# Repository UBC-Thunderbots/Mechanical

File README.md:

# Mechanical
Our mechanical CAD repository. To get started, please see follow the guide below:

## Setting Up with GitHub Desktop:
*Using GitHub Desktop is the simplest method. You're welcome to try other options

1. Download [GitHub Desktop](https://desktop.github.com/)
2. Create an account or login.
3. Go to the [Thunderbot's mechanical repository](https://github.com/UBC-Thunderbots/Mechanical) on GitHub.
4. Click on the green ```<> Code``` button and click: ```Open with GitHub Desktop```
5. Click Choose... and navigate to a local directory where you want to clone the repository. *Note that this location will be where a local copy of the entire CAD file will be stored.
6. Click Clone.
7. Ask to be added as a collaborator to the repository.

By now, you should have a local copy of the entire mechanical CAD folder.

## Workflow: Updating your local folder:

Before you make any changes to the mechanical assembly, it is important that you update your local CAD folder with any changes that may have been made by someone else so you are working with the most up-to-date mechanical assembly.

1. **On GitHub Desktop** click ```fetch```. This will _fetch_ any changes that have been made to the remote repository to you computer, without actually updating your local folder yet.

After fetching, you should be notified whether there are any merge conflicts. In other words, whether there have been any changes made to files that you have also modified on your local folder.

If there is a merge conflict:
1. Give-up. :(

If there is no merge conflict:
1. Click on ```Pull Origin``` and your local folder should automatically be updated to reflect any changes on the remote repository.

## Workflow: Updating your changes to the remote repository:

If you have any new changes, they should show up in your **GitHub Desktop** application under "Changed Files" - otherwise, you did something wrong.
1. Start off with ```committing to main```. Name the change you made under Summary _(e.g. New Dribbler Design)_.
2. After it commits successfully, the button at the top should read ```Push Origin```
3. Click on it. Do make sure that **nobody else is/was working on the same file you did - communicate this clearly before moving forward.**

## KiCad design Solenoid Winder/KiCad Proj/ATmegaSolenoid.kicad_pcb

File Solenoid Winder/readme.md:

# Solenoid Winding Machine - Standard Operating Procedure (SOP)
*Last revised: 7th June 2026 by Thomas Frew*

## Overview
*(Refer to CAD overviews of the winder and director assemblies)*

## Winding Instructions

### Wiring and Setup
Ensure the breadboard, solenoid winder motors, and Arduino Uno are wired as shown in the reference diagrams.
- Make all I/O connections shown in the table below. 
- Regarding the breadboard, buttons are LEFT, RIGHT, ENTER, BACK, from left to right.
- The motor controller board with the larger heatsink must be connected to the chuck motor*.

*Stepper motor connected to chuck: pins 1&3 are coil A and 4&6 are coil B. Stepper motor for lead screw: pins 1&4 are coil A and 3&6 are coil B.

### I/O Connections Table

| Input | Arduino Connection |
| :--- | :--- |
| Left_button | Digital Pin 0 |
| Right_button | Digital Pin 2 |
| Back_button | Digital Pin 3 |
| Enter_button | Digital Pin 4 |
| Lead_STEP | Digital Pin 5 |
| Lead_DIR | Digital Pin 6 |
| Chuck_STEP | Digital Pin 7 |
| Chuck_DIR | Digital Pin 8 |
| Lead_MS1 | Digital Pin 9 |
| Lead_MS2 | Digital Pin 10 |
| Lead_MS3 | Digital Pin 11 |
| +ve breadboard rail | +5V |
| -ve breadboard rail | GND |

### Step-by-Step Operation

1. Go to [https://github.com/Thoamy/SolenoidWinder](https://github.com/Thoamy/SolenoidWinder) and download `SolenoidWindingMachine_V1.ino`.
2. You will need the Arduino IDE to load the project onto your Arduino.
3. Ensure you have the correctly sized Chuck Adapter and Tailstock Adapter to match your Solenoid Housing.
4. Insert the Chuck Adapter and Tailstock Adapter into the Solenoid Housing (Chuck Adapter on the side with the coil escape hole), then install the assembly into the chuck/tailstock.
5. **Note on 3D Printing:** If you need to 3D print new adapters, ensure the Chuck adapter is printed oriented in a horizontal position (the position used) for torque transfer, and the Tailstock Adapter is printed in the vertical position for axial load bearing.
6. Load your roll of copper onto the Spool Holder subassembly. Use two nuts to hold the roll on, but do not tension the roll.
7. If necessary, loosen the captive nut on the Director Assembly and adjust the Director to be as close to the solenoid as possible, ensuring that the solenoid will never collide with the Director Assembly during rotation.
8. Feed the copper through the Director large hole, through 2-3 layers of foam, then through the Director small hole.
9. Use pliers to feed the copper through the escape hole of the Solenoid Housing.
10. Plug the Arduino USB into your computer (load the program if not done), and plug the 12V wall adapter barrel jack into the barrel jack adapter (plugged into the breadboard).
    - **⚠️ WARNING: DO NOT MIX +5V AND +12V OR YOU WILL FRY YOUR ARDUINO.**
11. During winding, make sure the first layer is super tight (slide the coils down with your hands if needed) so that the subsequent layers stack nicely on top.

## Controls
- **Left:** Moves left while rotating chuck.
- **Right:** Moves right while rotating chuck.
- **Enter + Right/Left (Hold):** Disengages the chuck and moves left/right.
- *Note:* If you need to unwind (or manually spin the motor for any reason), **turn off power and then unplug the motor first**.

## Troubleshooting
- **The motor is going the wrong way:** Swap a set of A/B lines on the breadboard (either 1 or 2, not both).
- **The chuck is jerking in different directions:** One of the coil lines has likely become unplugged from the breadboard.
- **The copper crossed over itself:** Turn off power, unplug the motor, unwind, plug back in, and try again.

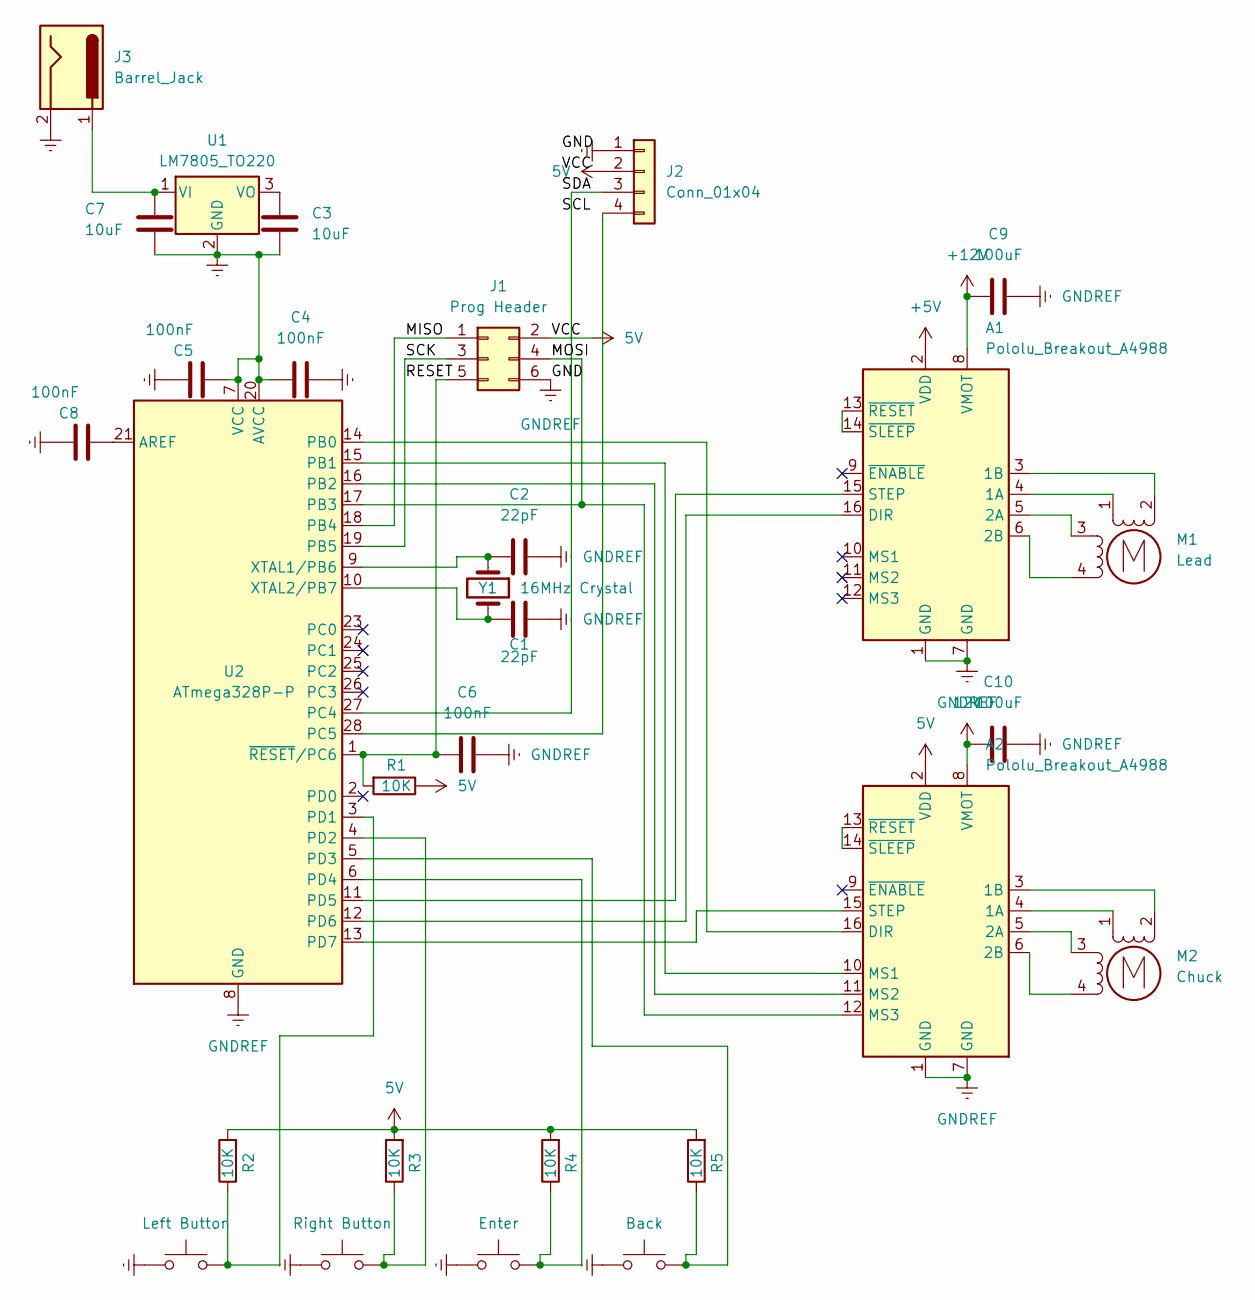
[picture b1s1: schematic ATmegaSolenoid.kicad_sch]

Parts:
A1, A2: Pololu_Breakout_A4988; Pololu_Breakout-16_15.2x20.3mm
C1, C2: 22pF; C_Disc_D5.0mm_W2.5mm_P2.50mm
C3, C7: 10uF; CP_Radial_D5.0mm_P2.00mm
C4, C5, C6, C8: 100nF; C_Disc_D5.0mm_W2.5mm_P2.50mm
C9, C10: 100uF; CP_Radial_D5.0mm_P2.00mm
J1: Prog Header; PinHeader_2x03_P2.54mm_Vertical
J2: Conn_01x04; PinHeader_1x04_P2.54mm_Vertical
J3: Barrel_Jack; BarrelJack_CUI_PJ-063AH_Horizontal
M1: Lead; PinHeader_1x04_P2.54mm_Vertical
M2: Chuck; PinHeader_1x04_P2.54mm_Vertical
R1, R2, R3, R4, R5: 10K; R_Axial_DIN0207_L6.3mm_D2.5mm_P10.16mm_Horizontal
SW1: Left Button; SW_PUSH_6mm_H4.3mm
SW2: Right Button; SW_PUSH_6mm_H4.3mm
SW3: Enter; SW_PUSH_6mm_H4.3mm
SW4: Back; SW_PUSH_6mm_H4.3mm
U1: LM7805_TO220; TO-220-3_Vertical
U2: ATmega328P-P; DIP-28_W7.62mm
Y1: 16MHz Crystal; Crystal_HC49-4H_Vertical

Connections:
5V: A2.2 (VDD), J1.2, J2.2, R1.1, R2.2, R3.2, R4.2, R5.2
12V: A2.8 (VMOT), C10.2
+5V: A1.2 (VDD)
+12V: A1.8 (VMOT), C9.2
/MISO: J1.1, U2.18 (PB4)
/MOSI: A2.12 (MS3), J1.4, U2.17 (PB3)
/RESET: J1.3, U2.19 (PB5)
GNDREF: A1.1 (GND), A1.7 (GND), A2.1 (GND), A2.7 (GND), C1.1, C2.1, C3.2, C4.1, C4.2, C5.1, C5.2, C6.1, C7.2, C8.2, C9.1, C10.1, J1.6, J2.1, J3.2, SW1.1, SW2.1, SW3.1, SW4.1, U1.2 (GND), U2.7 (VCC), U2.8 (GND), U2.20 (AVCC), U2.22 (GND)
unnamed: A1.4 (1A), M1.1
unnamed: A1.3 (1B), M1.2 (-_2)
unnamed: A1.5 (2A), M1.3
unnamed: A1.6 (2B), M1.4
unnamed: A1.16 (DIR), U2.12 (PD6)
unnamed: A1.15 (STEP), U2.11 (PD5)
unnamed: A1.13 (~RESET), A1.14 (~SLEEP)
unnamed: A2.4 (1A), M2.1
unnamed: A2.3 (1B), M2.2 (-_2)
unnamed: A2.5 (2A), M2.3
unnamed: A2.6 (2B), M2.4
unnamed: A2.16 (DIR), U2.14 (PB0)
unnamed: A2.10 (MS1), U2.15 (PB1)
unnamed: A2.11 (MS2), U2.16 (PB2)
unnamed: A2.15 (STEP), U2.13 (PD7)
unnamed: A2.13 (~RESET), A2.14 (~SLEEP)
unnamed: C6.2, J1.5, R1.2, U2.1 (~RESET/PC6)
unnamed: J2.3, U2.27 (PC4)
unnamed: J2.4, U2.28 (PC5)
unnamed: C7.1, J3.1, U1.1 (VI)
unnamed: C3.1, U1.3 (VO)
unnamed: C8.1, U2.21 (AREF)
unnamed: R2.1, SW1.2, U2.3 (PD1)
unnamed: R3.1, SW2.2, U2.4 (PD2)
unnamed: R5.1, SW4.2, U2.5 (PD3)
unnamed: R4.1, SW3.2, U2.6 (PD4)
unnamed: C2.2, U2.9 (XTAL1/PB6), Y1.1
unnamed: C1.2, U2.10 (XTAL2/PB7), Y1.2

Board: 2 copper layers, 29 parts (0 on the bottom side), 35 nets, no tracks yet.

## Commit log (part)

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2023-10-05 Main Files
2023-10-05 Original Files
2023-10-06 Testing
2023-10-06 local updates
    d
2023-10-07 README.md
2023-10-07 UPADATED FILES
2023-10-07 Chipper
    Merged new composite chipper design - Paul
2023-10-08 Top-level Cleanup
    Dribbler assembly was rebuilt and put back onto the top-level assembly.
2023-10-13 3D designed hexagon dampers
2023-10-14 uploaded elecstack.SLDPRT
    First prototype of one side of the elec stackup
2023-10-14 Finished 3D modelling damper backpack
2023-10-14 Rollers
2023-10-14 Cleaned up ELEC Stackup Assembly
2023-10-14 Countersink Jig 1.0
    Initial cad models and ideas for the the countersink jig - OCT 14
2023-10-14 Elec stackup.SLDPRT
2023-10-14 Created new part for kicker damper
2023-10-14 Inserted damper backpack to fixed kicker assembly
2023-10-15 Roller V2 Revised
2023-10-15 Top-level Cleanup
    Parts were added and mated.
2023-10-17 Revert "Merge branch 'main' of https://github.com/UBC-Thunderbots/Mechanical"
    This reverts commit ed1c370524d67ea6ddeae6a6308ed08a987dc605, reversing
    changes made to 8244fb1dfdcb226f472e6bfb38ca4f5b5e413f7a.
2023-10-17 Uploaded improved prototype + STL files
    - Added chamfer to prototype
    - Added STL file of prototype
    - Added 3mf file with appropriate settings
2023-10-17 Revert "Revert "Merge branch 'main' of https://github.com/UBC-Thunderbots/Mechanical""
    This reverts commit 3eda3d1fd0bff359699f58e27bb6a6186b4549ea.
2023-10-18 Added Elec Stack Prototype Folder
2023-10-19 Chipper Testing Rig
    Added CAD for chipper testing rig and updated the dimensions of the composite chipper
2023-10-21 Alternate Base Plate for chipping tests with solenoid adapter
2023-10-28 Updated Composite Chipper Design After Testing
    - made holes to M3
    - adjusted 3d printed connector and added slant
    - added elevated ground plate for testing
2023-10-28 Copied Dribbler assembly and put it into a new dribbler prototype folder
2023-11-04 Added files from dribbler damper prototype
2023-11-06 Created Crossbar motor attachment part
2023-11-10 Elecstack update
    Spring pin cad models for printing
2023-11-11 v2 Prototype Spring Pin
    replaced cad, STL, and cura file with new versions with adjusted dimensions
2023-11-18 Created new parts for the motor mounting crossbar
2023-11-18 update elecstack shelf
    using leah's PC, just made quick adjustment
2023-11-18 updated stl for shelftest elecstack
2023-11-18 Created assembly for prototype for internal gear crossbar
2023-11-19 Added Motor_Mount_Riser
2023-11-19 Created Modified_Baseplate
2023-11-19 Created Motor_Mount_Assembly
2023-11-19 Modified Motor_Mount_Assembly
2023-11-19 Created Motor_Mount_Riser_FL
2023-11-19 Created Motor_Mount_Riser_FR
2023-11-19 Updated Motor_Mount_Assembly
2023-11-23 New adapted version of roller
    Complete with spiral threads and conical shape
2023-11-25 Copied dribbler assembly components
    Made an internal gear prototype assembly using prototype crossbar with modified dribbler plates (that are copied) and other components from the dribbler assmebly.
2023-11-28 Update Motor Mount Risers
2023-11-29 Add Motor Mount Risers to Top Level 2024
2023-12-02 Jigs - Amtoj
2023-12-02 updated riser and added new test-rig folder
2023-12-29 Created new part for second CrossBar prototype
2023-12-30 Added captive nut holes and mirrored CrossBar_2.0
2024-01-02 Created Crossbar with C-clip and made a new assmebly
2024-01-16 adjusted dimensions of breakbeam housing; created new assembly
2024-01-16 Adjusted screw hole diameters
2024-01-16 Dribbler Test Rig
    created parts and assembly for dribbler test rig
2024-01-20 adjusted height
2024-01-21 Modified midplate
2024-01-24 Updated elecstack shelves
    Re-dimensioned some parts
2024-01-25 test rig files
2024-01-25 Revert "Merge branch 'main' of https://github.com/UBC-Thunderbots/Mechanical"
    This reverts commit f03819419704318146d4b567df81cfce3938429f, reversing
    changes made to 212a5b2abede681f053126597ebd719f1a9ad3d8.
2024-01-27 Kicker Prototypes CAD added
2024-01-27 screw for standoff
    screw attempt - still needs spiraled cut but solidworks doesn't want to for some reason
2024-01-27 New Basic Roller + Threaded Roller Molds
    Could potentially be used for polyurethane roller if needed
2024-01-27 Changed a few dimensions for dribbler plates
2024-01-27 Plunger prototype updates
2024-01-29 Updated dribbler damper and flexure
2024-01-29 Added offset standoff
2024-01-30 Adjusted Old Roller Design
    Slightly off-center, is ready for use with the new dribbler assembly
2024-01-31 Renamed assembly file
2024-02-01 Mold Assembly
2024-02-01 Moved roller mold files
2024-02-03 new solenoid + plunger
2024-02-03 top level
2024-02-03 Created mates for the dribbler subassembly and top level 2024 new change
2024-02-04 adjusted basic roller
2024-02-04 Dribbler subassembly
    - adjust dribbler plate bearing diameters to be 0.15mm greater
    - Added cable holders on the rear-face of the crossbar, but it interferes with the dribbler damper (will fix later)
2024-02-07 force push fix
    attempting to fix errors with the force push
2024-02-10 file fixes
2024-02-10 file fix 2
2024-02-11 Cable Holder
    Designed new cable holders for the dribbler
2024-02-11 file fixes
    deleted extra folders
2024-02-11 solenoid cover fix
    minor dimension change for solenoid cover
2024-02-16 Update BaseMidplateStandoff.SLDPRT
    Made cap holder part thinner
2024-02-16 More chipper stuff
    Changed solenoid to be more modular and added floor for plunger and minor adjustments to things for better tolerance.
2024-02-17 Kicker components
2024-02-17 Added stacked kicker assembly
2024-02-17 Amtoj First Push for changes on new top level Feb 17
2024-02-17 Updated Kicker Assembly
2024-02-18 TEST
2024-02-18 Kicker and Chipper Design Updates
2024-02-18 Create Damper prototype
    Harris
2024-02-18 Add files via upload
    Harris: This is my updated prototype
2024-02-19 Modified kicker head and kicker setup
2024-02-19 Updated Kicker head to have plunger sit in the middle of the kicker
2024-02-20 Added Cap Holder V2
2024-02-20 Updated hole sizing in cap holder and battery compartment
2024-02-22 New Roller Mold V6
    - RollerMold-V6
    - RollerMold-V6-Peg
    - RollerMold-V6-Hole
2024-02-23 Increased hole size for heat set inserts
2024-03-02 Chipper Update
    moved plunger above baseplate
2024-03-09 Solenoid and plunger update
    added return mech and minor adjustments
2024-03-09 Revised Dribbler V7
    Inverted hourglass shape, with the following parts:
    - Roller file
    - General mold file
    - Male/Female Parts
2024-03-09 Even Newer V7 Roller Mold
    Has adjusted shaft placement length
2024-03-09 Updated Kicker Solenoid Casing and Chipper
2024-03-09 UPDATE for Ben
2024-03-09 Update kicker plunger assembly
2024-03-09 Lightning Bolt addition and demension change Kicker Casing
2024-03-09 plunger
2024-03-09 Plunger Interference Correction
2024-03-09 solenoid change
2024-03-09 Final Countdown
2024-03-23 Plunger change
2024-03-23 more plunger changes
2024-03-24 Baseplate updated, Dribbler Mates fixed and updated
2024-03-29 Added New Breakbeam Control Board
    Added New Breakbeam Control Board to the repository, put it on the internal gear dribbler. New board had interference with the crossbar mounting screws, moved upper screws 1 mm closer to the near wall
2024-03-30 Breakbeam housing boards updated to new board version
2024-03-30 Added new composite kicker assembly
2024-03-30 Updated Crossbar to account for breakbeam wire path
2024-04-05 Updated Dribbler Crossbar, with new Breakbeam (again)
2024-04-06 Chipper angle update and minor solenoid adjustment
    added tolerance for spring and made new chipper assembly with different angle
2024-04-06 RasPi5 PCIE HAT V1
    Version of possible hat design found that might provide insight to dimensions, etc.
2024-04-07 Plunger Update
    made chipper composite plunger
2024-05-04 Chipper Angle Changes
    angle changed from 45 degrees to 39
2024-05-04 Chipper Arm
    made right hand config
2024-05-15 Improved Organization
    Changed some file names and created new folders and moved some files.
2024-05-16 UI Board
2024-05-20 Flexure Update
    Added TPU film on flexure
2024-05-21 added 4mm in height for dribbler plates
2024-05-22 Dribbler Roller V8
    - Changed radius to 5.75 mm (reduction from 6.25 mm)
    - Altered threads to have more smooth edges, lowered height of threads overall to reduce wear/tear over usage
2024-06-01 plunger and housing update
    changed plunger width and added vertical tolerance to housing
2024-06-03 Added new version of Motor Mount Riser to Top Level
2024-06-03 Cleaned up Motor Mount Riser files
2024-06-03 Updated heat insert hole sizing
2024-06-03 Added material around heat inserts
2024-06-03 Update Cap Holder V3 and Battery Compartment V3
2024-06-05 Created stabilizer for cap holders when installing heat inserts
2024-06-05 Dampers
2024-06-05 Roller V9
    Revamped higher, flattened threads and adjusted for internal gears; with manual tapering done from centre
2024-06-05 Added Battery Compartment with smaller holes
2024-06-05 Crossbar
2024-06-05 Roller V10
    Similar to V9, but with original tapered threads (thinner towards centre, like previous iterations)
2024-06-08 Chipper position update
    changed baseplate and shifted chipper and kicker back
2024-06-08 Wire Feeder V3 created
2024-06-10 Created White shell prototypes
2024-06-12 Updated mid-plate mounting hole locations
2024-06-12 Updated heat insert hole dimensions
2024-06-12 Breakbeam Housing Modified for wire path and extended cover
2024-06-13 Roller V11
    Final adjustments made to V9 with viable mold
2024-06-14 Roller V9 Final Updates
2024-06-14 V9 Mold Update
2024-06-15 Crossbar made more flexible
2024-06-15 CROSSBAR 6.1 IS THE ONE
2024-06-15 Updated Assembly
2024-06-15 Breakbeam Housing V3 Sandwich Cover
2024-06-16 Created new white shell prototypes
2024-06-16 Housing tolerance
2024-06-17 Updated Chipper Face Plate Jig
2024-06-17 Update Chipper Face Plate Jig
2024-06-17 Fully defined lightning bolt sketch
2024-06-18 Updated solenoid cover for printing
2024-06-22 extrude bossed ventilation holes
2024-06-22 Created wire band for internal gear dribbler
2024-06-22 Solenoid v5
2024-06-22 Adjusted crossbar2.0_C_clip
2024-06-22 Updated Top Level to Reflect Everyones Changes
    Added Ben's Wire Band
    Amtoj's solenoid Core Kicker and Chipper
    Re organized Top level to contain both the solenoid only kicker chipper and the previous design for easier switch ability
2024-06-22 New Solenoid v5
2024-06-22 Changes to dribbler
2024-06-23 deleted mates and moved chipper to solenoid folder
2024-06-23 Removed blank virtual assemblies
2024-06-23 MASSIVE FOLDER CLEANUP
    Long overdue folder sorting - still needs some work in a few folders (left the chipper stuff as is) but cleaned up quite a bit. Highlights:
    - Archived old designs from 2023
    - Renamed some files to follow convention/be more descriptive
    - Removed redundant files (especially from Dribbler folder)
    - Moved all jigs to the jig folder (including new ones)
    - Updated shell + vision pattern assembly in top level and white hull
2024-06-24 Rocky's changes
    fixed some dribbler components
2024-06-25 Cleaned up top level and sub assembly!
    Please pull and do not overwrite
2024-06-25 Cleaned up Roller V5 for manu, adjusted width for internal gear
2024-06-25 Renamed files for consistency
2024-06-28 Shorter Crossbar made even shorter :p
2024-06-29 Created Drawings from the Machined Components
2024-06-29 Updated dimensions and tolerancing
2024-06-29 Update dampers
2024-06-29 Roller Mold V5
2024-06-29 Added fillet to Modified Solenoid v6
2024-06-29 created a flattened prototype for the back part of the white shell
2024-07-01 Elec Stackup w/ UI
2024-07-01 Stackup Top Level (WIP)
2024-07-01 Create trace copy of white hull front prototype
2024-07-02 white hull challenge
    created assembly
2024-07-02 White hull challenge
    quarter pieces made. stl files created.
2024-07-02 updated white hull designs for printing
2024-07-04 Elec Stackup
2024-07-08 White Hull Challenge 2.0
2024-07-08 white hull back/left piece complete
    yay
2024-07-08 changed name of white hull folder
2024-07-10 adjusted ventilation hole tolerance for white hull
    for back and left piece
2024-07-11 created a backup plan for white hull challenge
    uses sketch dimensions for paper cutouts of white hull
